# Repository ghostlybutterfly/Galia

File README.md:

# Galia
Modular split ergonomic keyboard system with each half consisting of a central motherboard and a hot-swappable key cluster daughterboard to allow for maximum flexibility.

### Motherboard

- Current version: V0.2.
- Schematic [here](https://kicanvas.org/?repo=https%3A%2F%2Fgithub.com%2Fghostlybutterfly%2FGalia%2Fblob%2FV0_dev%2FMotherboard%2FMotherboard.kicad_sch). 
- Board layout [here](https://kicanvas.org/?repo=https%3A%2F%2Fgithub.com%2Fghostlybutterfly%2FGalia%2Ftree%2FV0_dev%2FMotherboard).
### Daughterboard (Cantaloupe)
Current version: N/A (wip).

## Disclaimer
This keyboard is licensed under [CERN-OHL-S-2.0](https://cern-ohl.web.cern.ch/) and is compatible with both [QMK Firmware](https://qmk.fm/) and [ZMK Firmware](https://zmk.dev).

## Key Features
### Motherboard
* Fully reversible, compact (32.0x48.0mm), and designed to fit onto the top inner corner of a split keyboard.
* On-board STM32G0B1CCU7 processor.
* ESD-protected USB-C input port and USB-C split comms ports with ideal diode configuration for reverse current protection on VBUS input.
* Connects to daughterboard through fully ESD-protected 2.54mm pitch 02x08 pogo header in [VIK](https://github.com/sadekbaroudi/vik) breakout layout with three additional GPIO and reset button pin.
* 4-layer (signal/ground/power/signal) PCB, guard ring around PCB, and star ground connection point in between USB port shields to reduce EMI.
* VBUS input rail limited to ~500mA and 5V output rail limited to ~188mA through the use of TPS2553-1 current limiting switches with reverse voltage protection. VBUS requires power cycling to restart the device upon overcurrent, +5V can be power-cycled through firmware with EN pin controlled through firmware to reduce RGB LED quiescent current draw.
* 2x05 1.27mm Samtec IDC SWD header for debugging purposes or [Paw-Connect](https://github.com/LeoDJ/Paw-Connect) TC-2030NL header - both fit in the same space and are effectively interchangeable
* On-board button[Acheron](https://acheronproject.com/reset_article_1/reset_article_1/#52-substituting-the-jfet) single-button reset circuit.
* JLC basic assembly compatible as long as USB ports are not soldered on.

### Daughterboard (TBC)
* Matrix scan planned to be implemented through 74HC595 SIPO shift registers for low power draw and compatibility with ZMK interrupt functionality.
* Also compatible with charlieplex, duplex, and standard matrix layouts.
* WS2812 and AP102 (QMK only) LED support.
* Additional [VIK](https://github.com/sadekbaroudi/vik) header support if desired.
* USART1, USART3, and reset circuit pins routed to pogo pin header to allow for relocation of split comms receptacle and reset button on daughterboard.

## Pogo header pinout
| Function/description                  | Pin name | Row 1 | Row 2 | Pin name | Function/description                  |
| ------------------------------------- | -------- | ----- | ----- | -------- | ------------------------------------- |
| Active high, hold for 1.6s for DFU    | N/A      | RST   | GPIO5 | B8       | SPI2 SCK/TIM4 CH3/I2C1 SCL            |
| USART1 TX/SPI2 MISO/I2C1 SCL/TIM1 CH3 | B6       | GPIO3 | GPIO4 | B7       | USART1 RX/SPI2 MOSI/TIM4 CH2/I2C1 SDA |
| 200mA max draw across system          | N/A      | 3V3   | GND   | N/A      | N/A                                   |
| I2C2 SDA                              | B4       | SDA   | SCL   | B3       | I2C2 SCL                              |
| SPI2 MOSI/TIM2 CH4                    | B11      | RGB   | 5V    | N/A      | 188mA max draw by daughterboard       |
| USART3 TX/SPI2 MISO/ACD IN10          | B2       | GPIO1 | MOSI  | A7       | SPI1 MOSI                             |
| USART3 RX/TIM3 CH3/TIM1 CH2N/ADC IN8  | B0       | GPIO2 | CS    | A4       | SPI1 NSS                              |
| SPI1 MISO                             | A6       | MISO  | SCK   | A5       | SPI1 SCK                              |

## VIK keyboard certification card
| Category                 | Classification          | Response           |
| -----------------------  | ----------------------- | ------------------ |
| FPC connector            | Required                | 2.54mm pogo header |
| Breakout pins            | Recommended             | :heavy_check_mark: |
| Supplies: SPI            | Strongly recommended    | :heavy_check_mark: |
| Supplies: I2C            | Strongly recommended    | :heavy_check_mark: |
| I2C on main PCB          | Discouraged             | :x:                |
| I2C pull ups             | Informative             | :x:                |
| Supplies: RGB            | Strongly recommended    | :heavy_check_mark: |
| Supplies: Extra GPIO 1   | Required                | Analog/Digital     |
| Supplies: Extra GPIO 2   | Required                | Analog/Digital     |

## Changelog
* 2026/09/26: V0.3 motherboard update complete. Reduced size again, rerouted board and changed shape slightly. Removed one mounting hole and centred the other between the USB ports. Changed input fuse and external +5V output to TPS2553-1 latching power switch with reverse voltage/current protection. Removed AO3401 and LMV321 discrete reverse current protection at VBUS input. Reduced size of VBUS and VSPLIT ferrite bead and transistors in the Acheron reset circuit. Made Acheron reset circuit reach DFU faster. 
* 2026/09/21: V0.2 motherboard update complete. Significantly decreased size. GPIO3, GPIO4 and GPIO5 pins changed. Increased size of pogo pin header pads. Removed extra IO header. Replaced 2x03 2.54mm programming header and TC2030-NL with 2x05 1.27mm Samtec IDC header. Replaced reset switch with smaller Alps SKSNLP mid-mount switch. Added layer marker. Changed repository file structure.
* 2026/09/17: Fixed gap in guard rail.
* 2026/09/16: V0.1 motherboard initial commit.

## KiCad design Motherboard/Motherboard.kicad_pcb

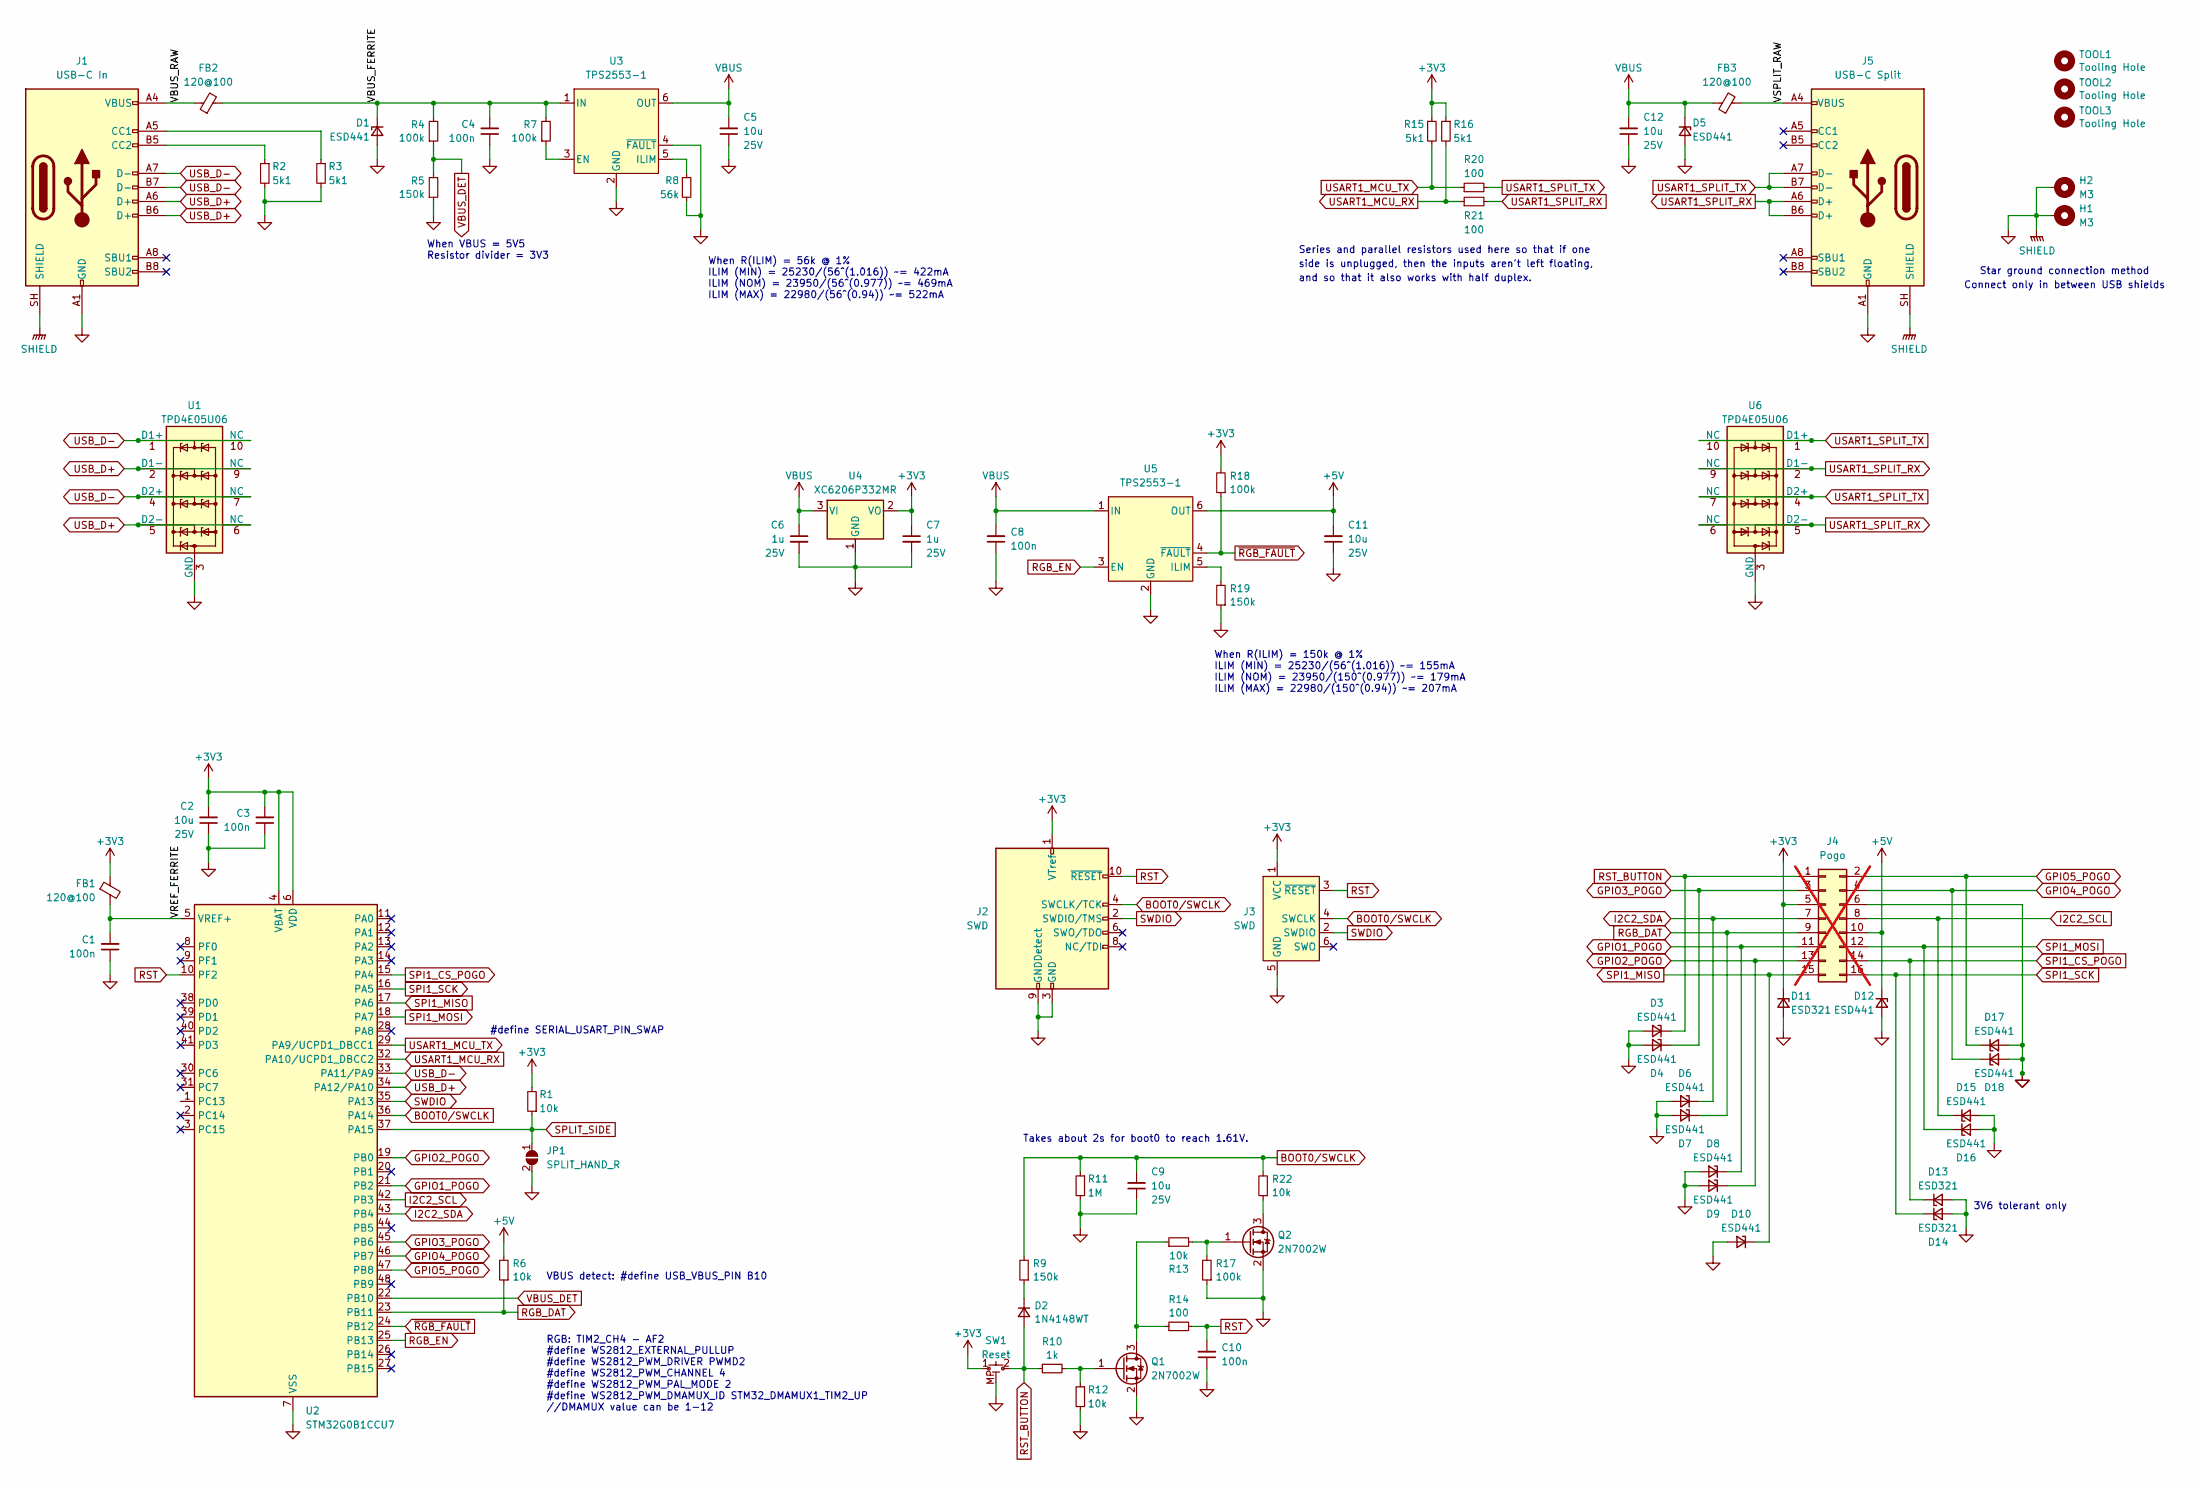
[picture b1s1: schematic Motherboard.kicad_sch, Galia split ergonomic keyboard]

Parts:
C1, C3, C4, C8, C10: 100n; C_0402_1005Metric; Rating 50V; MPN CL05B104KB54PNC; LCSC C307331
C2, C5, C9, C11, C12: 10u; C_0603_1608Metric; Rating 25V; MPN CL10A106MA8NRNC; LCSC C96446
C6, C7: 1u; C_0402_1005Metric; Rating 25V; MPN CL05A105KA5NQNC; LCSC C52923
D1, D3, D4, D5, D6, D7, D8, D9, D10, D12, D15, D16, D17, D18: ESD441; X1SON_0.6x1mm_P0.65mm_Texas_DPY0002A; MPN ESD441DPYR; LCSC C53161160
D2: 1N4148WT; D_SOD-523; MPN 1N4148WT; LCSC C7420320
D11, D13, D14: ESD321; X1SON_0.6x1mm_P0.65mm_Texas_DPY0002A; MPN ESD321DPYR; LCSC C2868952
FB1, FB2, FB3: 120@100; L_0402_1005Metric; MPN MPZ1005S121ET000; LCSC C275477
H1, H2: M3; MountingHole_3.2mm_M3_Pad_Via; MPN N/A; LCSC N/A
J1: USB-C In; USB_C_Receptacle_Molex_2169900001; MPN GT-USB-7014D; LCSC C2843969
J2: SWD; PinHeader_2x05_P1.27mm_Vertical_Samtec-FTSH-105-01-L-D-K; MPN FTSH-105-01-L-D-K; LCSC N/A
J3: SWD; Paw-Connect_RevB_TC2030-IDC-NL_2x03_P1.27mm_Vertical
J4: Pogo; PinHeader_2x08_2.54mm_MillMax_PogoTarget_419-10-216-00-0010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; MPN 419-10-214-00-001000; LCSC N/A; not fitted
J5: USB-C Split; USB_C_Receptacle_Molex_2169900001; MPN GT-USB-7014D; LCSC C2843969
JP1: SPLIT_HAND_R; SolderJumper-2_P1.2mm_Open_Pad1.0x1.4mm; MPN N/A; LCSC N/A
Q1, Q2: 2N7002W; SOT-323_SC-70-3; MPN 2N7002W; LCSC C7420322
R1, R6, R12, R13, R22: 10k; R_0402_1005Metric; MPN 0402WGF1002TCE; LCSC C25744
R2, R3, R15, R16: 5k1; R_0402_1005Metric; MPN 0402WGF5101TCE; LCSC C25905
R4, R7, R17, R18: 100k; R_0402_1005Metric; MPN 0402WGF1003TCE; LCSC C25741
R5, R9, R19: 150k; R_0402_1005Metric; MPN 0402WGF1503TCE; LCSC C25755
R8: 56k; R_0402_1005Metric; MPN 0402WGF5602TCE; LCSC C25796
R10: 1k; R_0402_1005Metric; MPN 0402WGF1001TCE; LCSC C11702
R11: 1M; R_0402_1005Metric; MPN 0402WGF1004TCE; LCSC C26083
R14, R20, R21: 100; R_0402_1005Metric; MPN 0402WGF1000TCE; LCSC C25076
SW1: Reset; SW_Alps_SKSNLM_SKSNLP; MPN SKSNLPE010; LCSC C53113391
TOOL1, TOOL2, TOOL3: Tooling Hole; MountingHole_JLC-Tooling; MPN N/A; LCSC N/A
U1, U6: TPD4E05U06; USON-10_2.5x1.0mm_P0.5mm; MPN TPD4E05U06QDQARQ1; LCSC C81353
U2: STM32G0B1CCU7; QFN-48-1EP_7x7mm_P0.5mm_EP5.6x5.6mm; MPN STM32G0B1CCU7; LCSC C29759424
U3, U5: TPS2553-1; WSON-6-1EP_2x2mm_P0.65mm_EP1x1.6mm
U4: XC6206P332MR; SOT-23-3; MPN XC6206P332MR-G; LCSC C5446

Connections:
+3V3: C2.2, C3.2, C7.1, D11.1 (K), FB1.1, J2.1 (VTref), J3.1 (VCC), J4.5, R1.2, R15.1, R16.1, R18.2, SW1.1 (A), U2.4 (VBAT), U2.6 (VDD), U4.2 (VO)
+5V: C11.2, D12.1 (K), J4.10, R6.2, U5.6 (OUT)
/VBUS_FERRITE: C4.2, D1.1 (K), FB2.2, R4.2, R7.2, U3.1 (IN)
/VBUS_RAW: FB2.1, J1.A4 (VBUS), J1.A9 (VBUS), J1.B4 (VBUS), J1.B9 (VBUS)
/VREF_FERRITE: C1.2, FB1.2, U2.5 (VREF+)
/VSPLIT_RAW: FB3.2, J5.A4 (VBUS), J5.A9 (VBUS), J5.B4 (VBUS), J5.B9 (VBUS)
BOOT0/SWCLK: C9.2, J2.4 (SWCLK/TCK), J3.4 (SWCLK), R9.2, R11.1, R22.2, U2.36 (PA14)
GND: C1.1, C2.1, C3.1, C4.1, C5.1, C6.2, C7.2, C8.1, C9.1, C10.1, C11.1, C12.1, D1.2 (A), D3.2 (A), D4.2 (A), D5.2 (A), D6.2 (A), D7.2 (A), D8.2 (A), D9.2 (A), D10.2 (A), D11.2 (A), D12.2 (A), D13.2 (A), D14.2 (A), D15.2 (A), D16.2 (A), D17.2 (A), D18.2 (A), H1.1 (1_1), H2.1 (1_1), J1.A1 (GND), J1.A12 (GND), J1.B1 (GND), J1.B12 (GND), J1.SH (SHIELD), J2.3 (GND), J2.5 (GND), J2.9 (GNDDetect), J3.5 (GND), J4.6, J5.A1 (GND), J5.A12 (GND), J5.B1 (GND), J5.B12 (GND), J5.SH (SHIELD), JP1.2 (B), Q1.2 (S), Q2.2 (S), R2.2, R3.2, R5.1, R8.2, R11.2, R12.2, R17.1, R19.1, SW1.MP (A), U1.3 (GND), U1.8 (GND), U2.7 (VSS), U2.49 (VSS), U3.2 (GND), U3.4 (~FAULT), U3.7 (EP), U4.1 (GND), U5.2 (GND), U5.7 (EP), U6.3 (GND), U6.8 (GND)
GPIO1_POGO: D8.1 (K), J4.11, U2.21 (PB2)
GPIO2_POGO: D9.1 (K), J4.13, U2.19 (PB0)
GPIO3_POGO: D4.1 (K), J4.3, U2.45 (PB6)
GPIO4_POGO: D18.1 (K), J4.4, U2.46 (PB7)
GPIO5_POGO: D17.1 (K), J4.2, U2.47 (PB8)
I2C2_SCL: D15.1 (K), J4.8, U2.42 (PB3)
I2C2_SDA: D6.1 (K), J4.7, U2.43 (PB4)
unnamed: D2.1 (K), R9.1
unnamed: J1.A5 (CC1), R3.1
unnamed: J1.B5 (CC2), R2.1
unnamed: Q1.3 (D), R13.1, R14.1
unnamed: Q1.1 (G), R10.2, R12.1
unnamed: Q2.3 (D), R22.1
unnamed: Q2.1 (G), R13.2, R17.2
unnamed: R7.1, U3.3 (EN)
unnamed: R8.1, U3.5 (ILIM)
unnamed: R19.2, U5.5 (ILIM)
RGB_DAT: D7.1 (K), J4.9, R6.1, U2.23 (PB11)
RGB_EN: U2.25 (PB13), U5.3 (EN)
RST: C10.2, J2.10 (~RESET), J3.3 (~RESET), R14.2, U2.10 (PF2)
RST_BUTTON: D2.2 (A), D3.1 (K), J4.1, R10.1, SW1.2 (B)
SPI1_CS_POGO: D13.1 (K), J4.14, U2.15 (PA4)
SPI1_MISO: D10.1 (K), J4.15, U2.17 (PA6)
SPI1_MOSI: D16.1 (K), J4.12, U2.18 (PA7)
SPI1_SCK: D14.1 (K), J4.16, U2.16 (PA5)
SPLIT_SIDE: JP1.1 (A), R1.1, U2.37 (PA15)
SWDIO: J2.2 (SWDIO/TMS), J3.2 (SWDIO), U2.35 (PA13)
USART1_MCU_RX: R16.2, R21.1, U2.32 (PA10/UCPD1_DBCC2)
USART1_MCU_TX: R15.2, R20.1, U2.29 (PA9/UCPD1_DBCC1)
USART1_SPLIT_RX: J5.A6 (D+), J5.B6 (D+), R21.2, U6.2 (D1-), U6.5 (D2-), U6.6 (NC), U6.9 (NC)
USART1_SPLIT_TX: J5.A7 (D-), J5.B7 (D-), R20.2, U6.1 (D1+), U6.4 (D2+), U6.7 (NC), U6.10 (NC)
USB_D+: J1.A6 (D+), J1.B6 (D+), U1.2 (D1-), U1.5 (D2-), U1.6 (NC), U1.9 (NC), U2.34 (PA12/PA10)
USB_D-: J1.A7 (D-), J1.B7 (D-), U1.1 (D1+), U1.4 (D2+), U1.7 (NC), U1.10 (NC), U2.33 (PA11/PA9)
VBUS: C5.2, C6.1, C8.2, C12.2, D5.1 (K), FB3.1, U3.6 (OUT), U4.3 (VI), U5.1 (IN)
VBUS_DET: R4.1, R5.2, U2.22 (PB10)
~RGB_FAULT: R18.1, U2.24 (PB12), U5.4 (~FAULT)

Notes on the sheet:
3V6 tolerant only
#define WS2812_EXTERNAL_PULLUP #define WS2812_PWM_DRIVER PWMD2 #define WS2812_PWM_CHANNEL 4 #define WS2812_PWM_PAL_MODE 2 #define WS2812_PWM_DMAMUX_ID STM32_DMAMUX1_TIM2_UP //DMAMUX value can be 1-12
When R(ILIM) = 56k @ 1% ILIM (MIN) = 25230/(56^(1.016)) ~= 422mA ILIM (NOM) = 23950/(56^(0.977)) ~= 469mA ILIM (MAX) = 22980/(56^(0.94)) ~= 522mA
Takes about 2s for boot0 to reach 1.61V.
RGB: TIM2_CH4 - AF2
Series and parallel resistors used here so that if one
VBUS detect: #define USB_VBUS_PIN B10
side is unplugged, then the inputs aren't left floating,
and so that it also works with half duplex.
When VBUS = 5V5 Resistor divider = 3V3
Connect only in between USB shields
#define SERIAL_USART_PIN_SWAP
When R(ILIM) = 150k @ 1% ILIM (MIN) = 25230/(56^(1.016)) ~= 155mA ILIM (NOM) = 23950/(150^(0.977)) ~= 179mA ILIM (MAX) = 22980/(150^(0.94)) ~= 207mA
Star ground connection method

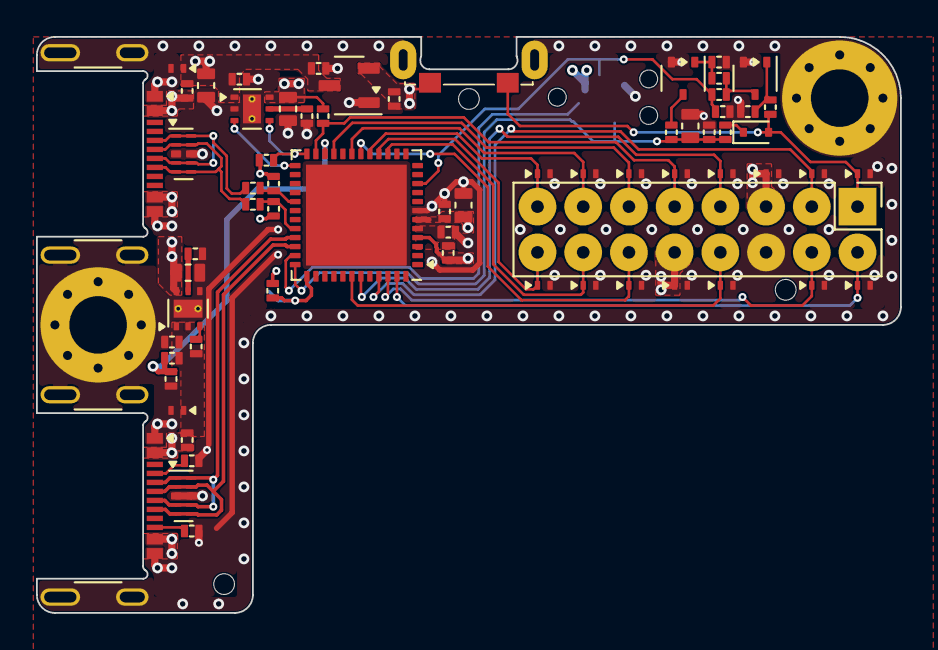
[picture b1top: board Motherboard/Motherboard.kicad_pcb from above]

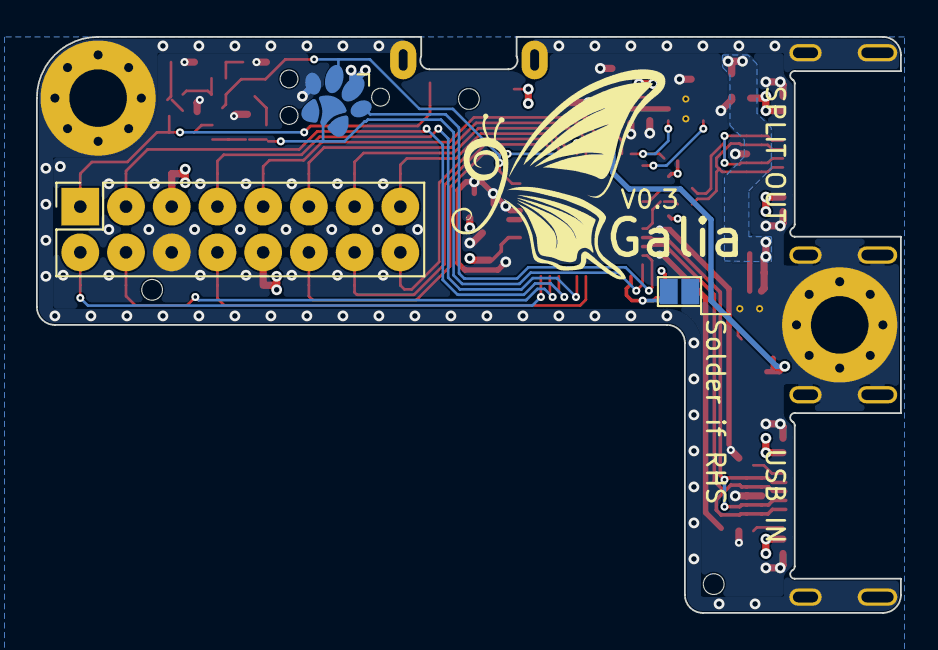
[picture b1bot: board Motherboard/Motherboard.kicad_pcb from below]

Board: 4 copper layers, 48.0 x 32.0 mm, 74 parts (3 on the bottom side), 44 nets.

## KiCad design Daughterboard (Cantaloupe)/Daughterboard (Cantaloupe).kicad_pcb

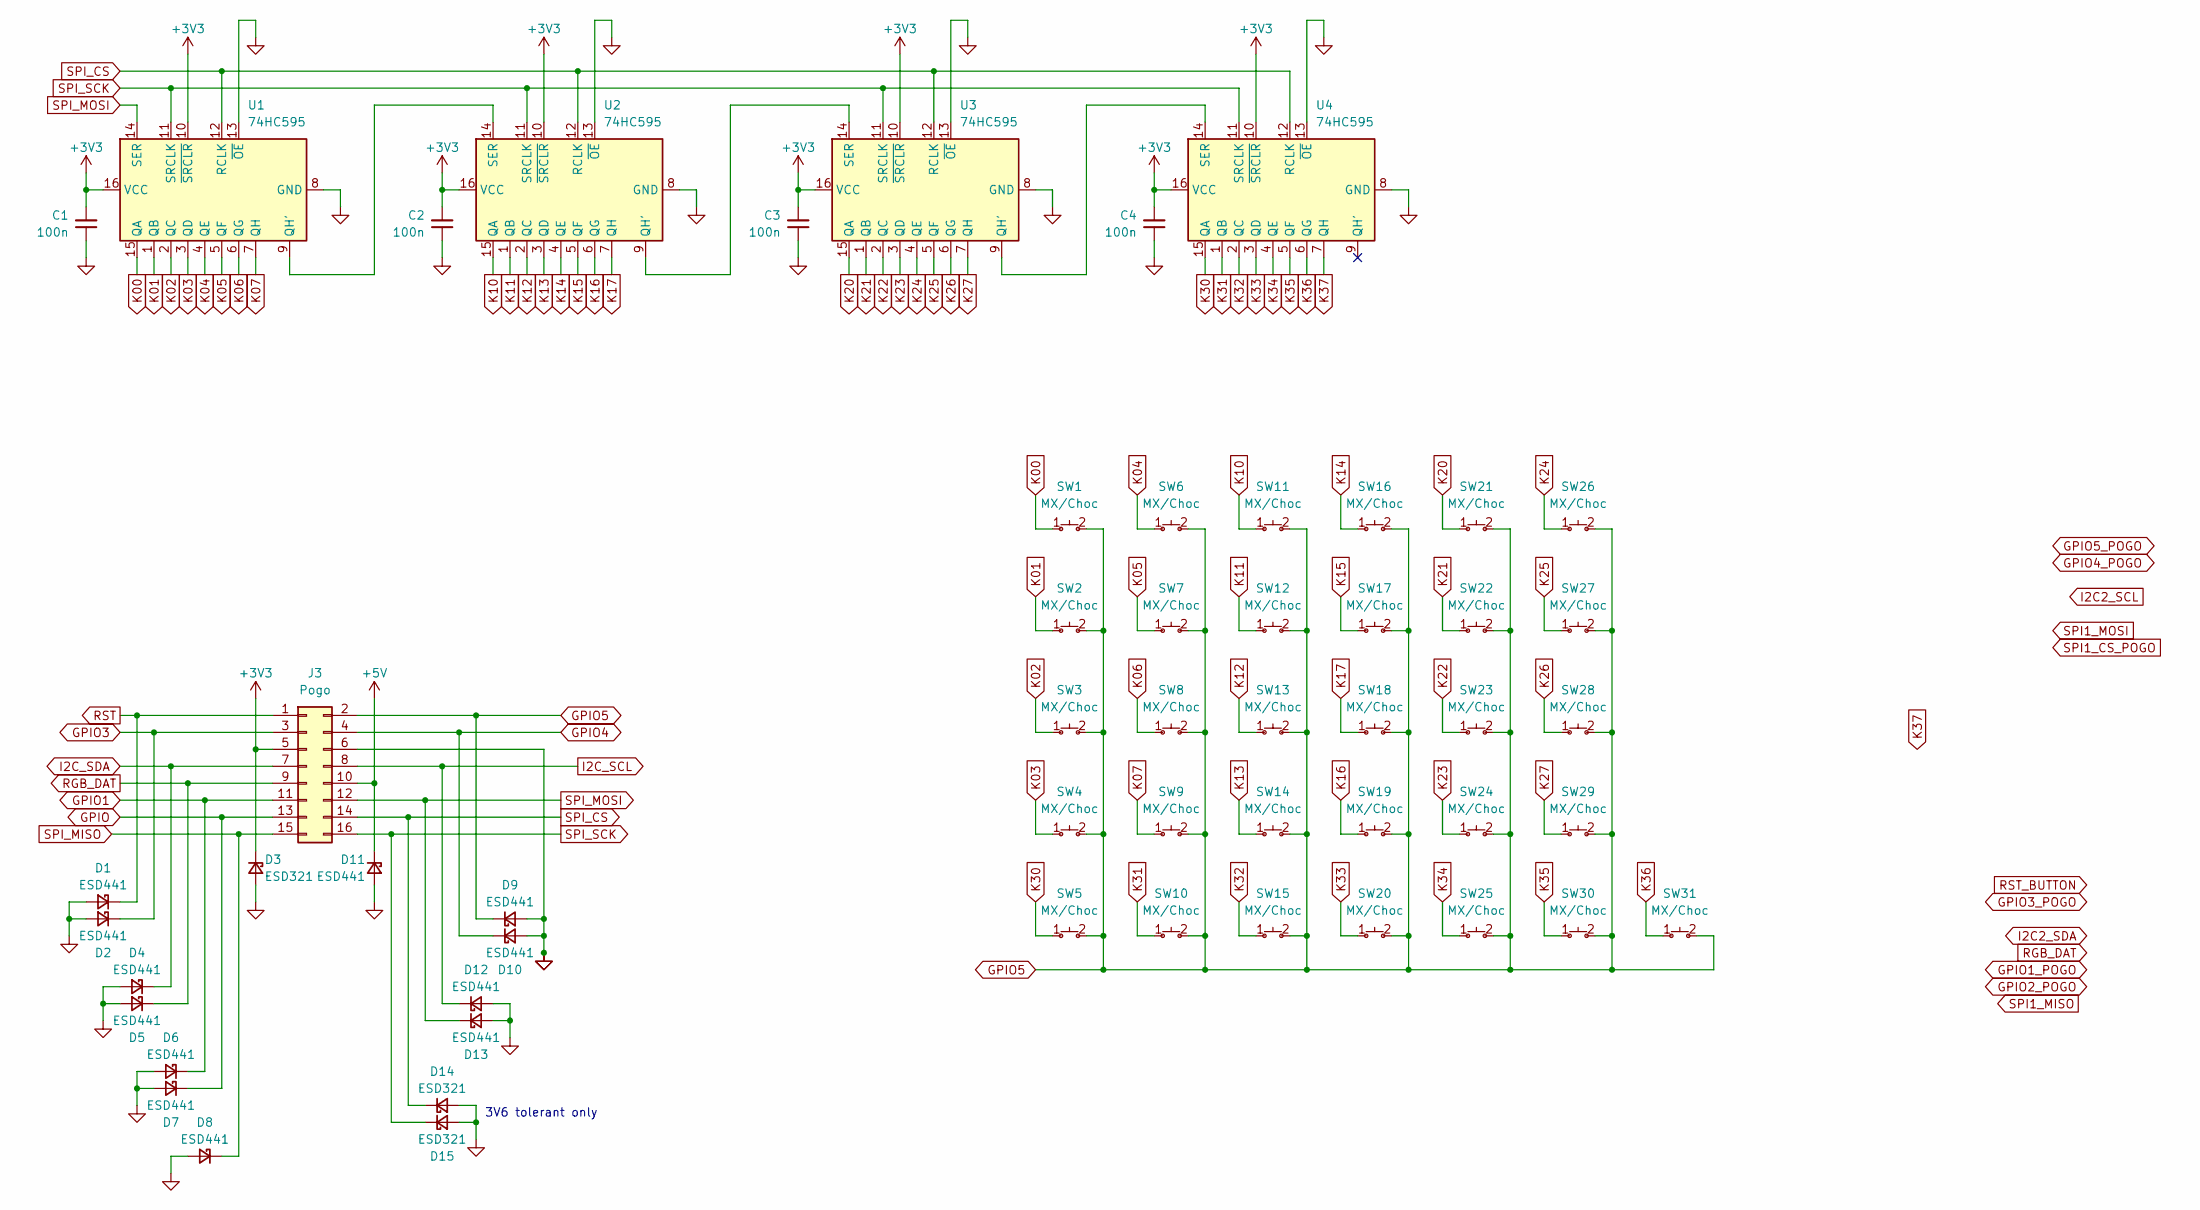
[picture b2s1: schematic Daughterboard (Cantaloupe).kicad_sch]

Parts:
C1, C2, C3, C4: 100n; C_0402_1005Metric; Voltage 50V; MPN CL05B104KB54PNC; LCSC C307331
D1, D2, D4, D5, D6, D7, D8, D9, D10, D11, D12, D13: ESD441; X1SON_0.6x1mm_P0.65mm_Texas_DPY0002A; MPN ESD441DPYR; LCSC C53161160
D3, D14, D15: ESD321; X1SON_0.6x1mm_P0.65mm_Texas_DPY0002A; MPN ESD321DPYR; LCSC C2868952
J3: Pogo; PinHeader_2x08_2.54mm_MillMax_PogoPin_823-22-016-10-002101_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; MPN 419-10-214-00-001000
SW1, SW2, SW3, SW4, SW5, SW6, SW7, SW8, SW9, SW10, SW11, SW12, SW13, SW14, SW15, SW16, SW17, SW18, SW19, SW20, SW21, SW22, SW23, SW24, SW25, SW26, SW27, SW28, SW29, SW30, SW31: MX/Choc; SW_MX-Choc_1U_Hotswap_Flippable
U1, U2, U3, U4: 74HC595; DHVQFN-16-1EP_2.5x3.5mm_P0.5mm_EP1x2mm; MPN 74HC595BQ,115; LCSC C730243

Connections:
+3V3: C1.2, C2.2, C3.2, C4.2, D3.1 (K), J3.5, U1.10 (~SRCLR), U1.16 (VCC), U2.10 (~SRCLR), U2.16 (VCC), U3.10 (~SRCLR), U3.16 (VCC), U4.10 (~SRCLR), U4.16 (VCC)
+5V: D11.1 (K), J3.10
GND: C1.1, C2.1, C3.1, C4.1, D1.2 (A), D2.2 (A), D3.2 (A), D4.2 (A), D5.2 (A), D6.2 (A), D7.2 (A), D8.2 (A), D9.2 (A), D10.2 (A), D11.2 (A), D12.2 (A), D13.2 (A), D14.2 (A), D15.2 (A), J3.6, U1.8 (GND), U1.13 (~OE), U1.17 (EP), U2.8 (GND), U2.13 (~OE), U2.17 (EP), U3.8 (GND), U3.13 (~OE), U3.17 (EP), U4.8 (GND), U4.13 (~OE), U4.17 (EP)
GPIO: D7.1 (K), J3.13
GPIO1: D6.1 (K), J3.11
GPIO3: D2.1 (K), J3.3
GPIO4: D10.1 (K), J3.4
GPIO5: D9.1 (K), J3.2, SW1.2 (B), SW2.2 (B), SW3.2 (B), SW4.2 (B), SW5.2 (B), SW6.2 (B), SW7.2 (B), SW8.2 (B), SW9.2 (B), SW10.2 (B), SW11.2 (B), SW12.2 (B), SW13.2 (B), SW14.2 (B), SW15.2 (B), SW16.2 (B), SW17.2 (B), SW18.2 (B), SW19.2 (B), SW20.2 (B), SW21.2 (B), SW22.2 (B), SW23.2 (B), SW24.2 (B), SW25.2 (B), SW26.2 (B), SW27.2 (B), SW28.2 (B), SW29.2 (B), SW30.2 (B), SW31.2 (B)
I2C_SCL: D12.1 (K), J3.8
I2C_SDA: D4.1 (K), J3.7
K00: SW1.1 (A), U1.15 (QA)
K01: SW2.1 (A), U1.1 (QB)
K02: SW3.1 (A), U1.2 (QC)
K03: SW4.1 (A), U1.3 (QD)
K04: SW6.1 (A), U1.4 (QE)
K05: SW7.1 (A), U1.5 (QF)
K06: SW8.1 (A), U1.6 (QG)
K07: SW9.1 (A), U1.7 (QH)
K10: SW11.1 (A), U2.15 (QA)
K11: SW12.1 (A), U2.1 (QB)
K12: SW13.1 (A), U2.2 (QC)
K13: SW14.1 (A), U2.3 (QD)
K14: SW16.1 (A), U2.4 (QE)
K15: SW17.1 (A), U2.5 (QF)
K16: SW19.1 (A), U2.6 (QG)
K17: SW18.1 (A), U2.7 (QH)
K20: SW21.1 (A), U3.15 (QA)
K21: SW22.1 (A), U3.1 (QB)
K22: SW23.1 (A), U3.2 (QC)
K23: SW24.1 (A), U3.3 (QD)
K24: SW26.1 (A), U3.4 (QE)
K25: SW27.1 (A), U3.5 (QF)
K26: SW28.1 (A), U3.6 (QG)
K27: SW29.1 (A), U3.7 (QH)
K30: SW5.1 (A), U4.15 (QA)
K31: SW10.1 (A), U4.1 (QB)
K32: SW15.1 (A), U4.2 (QC)
K33: SW20.1 (A), U4.3 (QD)
K34: SW25.1 (A), U4.4 (QE)
K35: SW30.1 (A), U4.5 (QF)
K36: SW31.1 (A), U4.6 (QG)
K37: U4.7 (QH)
unnamed: U1.9 (QH'), U2.14 (SER)
unnamed: U2.9 (QH'), U3.14 (SER)
unnamed: U3.9 (QH'), U4.14 (SER)
RGB_DAT: D5.1 (K), J3.9
RST: D1.1 (K), J3.1
SPI_CS: D14.1 (K), J3.14, U1.12 (RCLK), U2.12 (RCLK), U3.12 (RCLK), U4.12 (RCLK)
SPI_MISO: D8.1 (K), J3.15
SPI_MOSI: D13.1 (K), J3.12, U1.14 (SER)
SPI_SCK: D15.1 (K), J3.16, U1.11 (SRCLK), U2.11 (SRCLK), U3.11 (SRCLK), U4.11 (SRCLK)

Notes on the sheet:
3V6 tolerant only

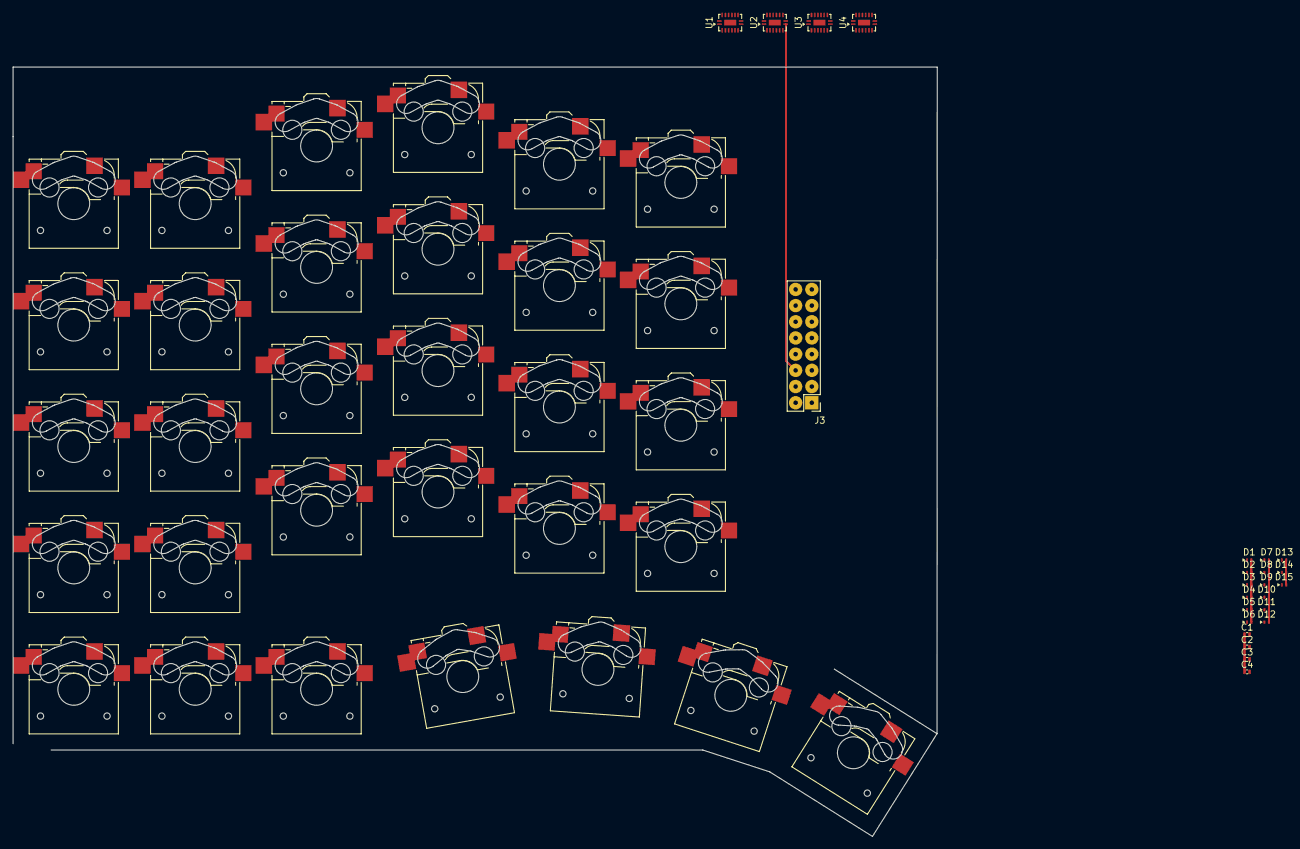
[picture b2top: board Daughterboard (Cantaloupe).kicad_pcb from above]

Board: 2 copper layers, 55 parts (0 on the bottom side), 50 nets.

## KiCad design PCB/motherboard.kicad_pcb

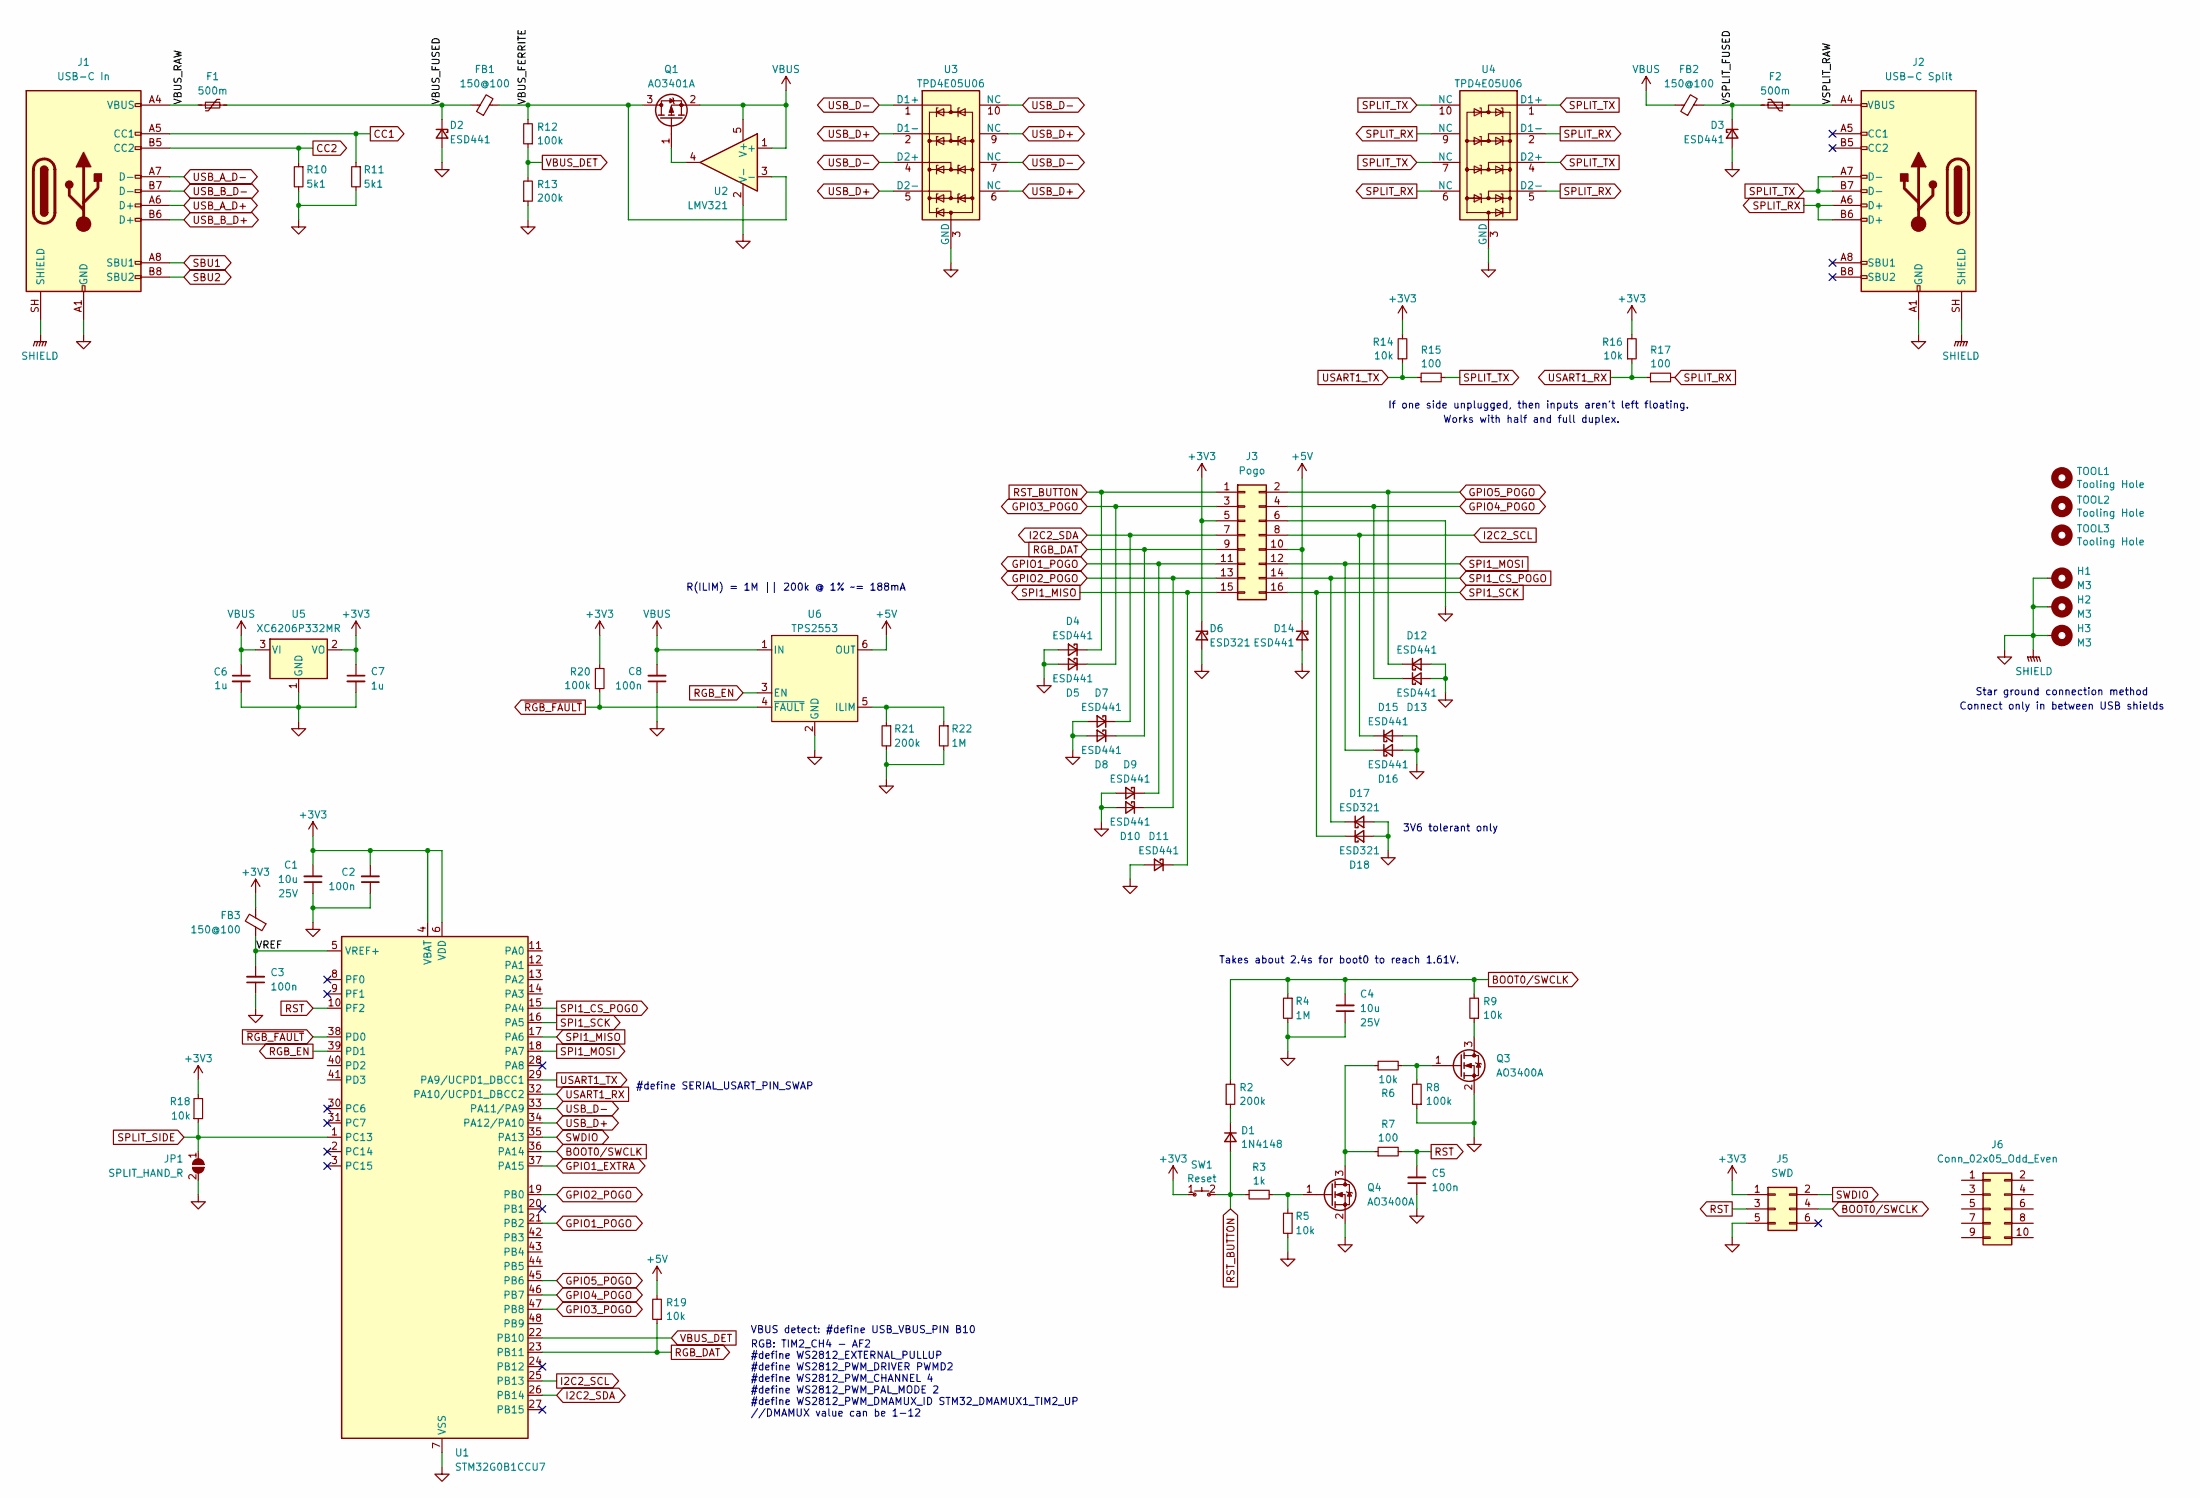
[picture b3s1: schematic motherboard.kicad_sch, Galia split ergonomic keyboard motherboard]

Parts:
C1, C4: 10u; C_0603_1608Metric; Voltage 25V; MPN CL10A106MA8NRNC; LCSC C96446
C2, C3, C5, C8: 100n; C_0402_1005Metric; Voltage 50V; MPN CL05B104KB54PNC; LCSC C307331
C6, C7: 1u; C_0402_1005Metric; Voltage 25V; MPN CL05A105KA5NQNC; LCSC C52923
D1: 1N4148; D_SOD-323; MPN 1N4148WS; LCSC C2128
D2, D3, D4, D5, D7, D8, D9, D10, D11, D12, D13, D14, D15, D16: ESD441; Texas_DPY0002A_0.6x1mm_P0.65mm; MPN ESD441DPYR; LCSC C53161160
D6, D17, D18: ESD321; Texas_DPY0002A_0.6x1mm_P0.65mm; MPN ESD321DPYR; LCSC C2868952
F1, F2: 500m; Fuse_0603_1608Metric; MPN MF-FSMF050X-2; LCSC C210357
FB1, FB2, FB3: 150@100; L_0603_1608Metric; MPN MPZ1608Y151BTD25; LCSC C404681
H1, H2, H3: M3; MountingHole_3.2mm_M3_Pad_Via
J1: USB-C In; HRO_TYPE-C-31-M-13x; MPN TYPE-C-31-M-13C; LCSC C2848620
J2: USB-C Split; HRO_TYPE-C-31-M-13x; MPN TYPE-C-31-M-13C; LCSC C2848620
J3: Pogo; MillMax_2x08_2.54mm_Pogo_Target_419-10-216-00-001000-Double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; MPN 419-10-214-00-001000
J5: SWD; PinHeader_2x03_P2.54mm_Vertical-Double_Sided
J6: Conn_02x05_Odd_Even
JP1: SPLIT_HAND_R; SolderJumper-2_P1.2mm_Open_Pad1.0x1.4mm
Q1: AO3401A; SOT-23-3; MPN AO3401A; LCSC C15127
Q3, Q4: AO3400A; SOT-23-3; MPN AO3400A; LCSC C20917
R2, R13, R21: 200k; R_0402_1005Metric; MPN 0402WGF2003TCE; LCSC C25764
R3: 1k; R_0402_1005Metric; MPN 0402WGF1001TCE; LCSC C11702
R4, R22: 1M; R_0402_1005Metric; MPN 0402WGF1004TCE; LCSC C26083
R5, R6, R9, R14, R16, R18, R19: 10k; R_0402_1005Metric; MPN 0402WGF1002TCE; LCSC C25744
R7, R15, R17: 100; R_0402_1005Metric; MPN 0402WGF1000TCE; LCSC C25076
R8, R12, R20: 100k; R_0402_1005Metric; MPN 0402WGF1003TCE; LCSC C25741
R10, R11: 5k1; R_0402_1005Metric; MPN 0402WGF5101TCE; LCSC C25905
SW1: Reset; SW_Alps_SKHLLA-Double_Sided; MPN SKHLLA; LCSC C318884
TOOL1, TOOL2, TOOL3: Tooling Hole; MountingHole_JLC-Tooling
U1: STM32G0B1CCU7; QFN-48-1EP_7x7mm_P0.5mm_EP5.6x5.6mm; MPN STM32G0B1CCU7; LCSC C29759424
U2: LMV321; SOT-23-5; MPN LMV321IDBVR; LCSC C7972
U3, U4: TPD4E05U06; USON-10_2.5x1.0mm_P0.5mm; MPN TPD4E05U06QDQARQ1; LCSC C81353
U5: XC6206P332MR; SOT-23-3; MPN XC6206P332MR-G; LCSC C5446
U6: TPS2553; SOT-23-6; MPN TPS2553DDBVR; LCSC C521201

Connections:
+3V3: C1.2, C2.2, C7.1, D6.1 (K), FB3.2, J3.5, J5.1, R14.2, R16.2, R18.2, R20.2, SW1.1 (A), U1.4 (VBAT), U1.6 (VDD), U5.2 (VO)
+5V: D14.1 (K), J3.10, R19.2, U6.6 (OUT)
/VBUS_FERRITE: FB1.2, Q1.3 (D), R12.2, U2.3 (-)
/VBUS_FUSED: D2.1 (K), F1.2, FB1.1
/VBUS_RAW: F1.1, J1.A4 (VBUS), J1.A9 (VBUS), J1.B4 (VBUS), J1.B9 (VBUS)
/VREF: C3.2, FB3.1, U1.5 (VREF+)
/VSPLIT_FUSED: D3.1 (K), F2.2, FB2.2
/VSPLIT_RAW: F2.1, J2.A4 (VBUS), J2.A9 (VBUS), J2.B4 (VBUS), J2.B9 (VBUS)
BOOT0/SWCLK: C4.2, J5.4, R2.2, R4.1, R9.2, U1.36 (PA14)
CC1: J1.A5 (CC1), R11.1
CC2: J1.B5 (CC2), R10.1
GND: C1.1, C2.1, C3.1, C4.1, C5.1, C6.2, C7.2, C8.1, D2.2 (A), D3.2 (A), D4.2 (A), D5.2 (A), D6.2 (A), D7.2 (A), D8.2 (A), D9.2 (A), D10.2 (A), D11.2 (A), D12.2 (A), D13.2 (A), D14.2 (A), D15.2 (A), D16.2 (A), D17.2 (A), D18.2 (A), H1.1 (1_1), H2.1 (1_1), H3.1 (1_1), J1.A1 (GND), J1.A12 (GND), J1.B1 (GND), J1.B12 (GND), J1.SH (SHIELD), J2.A1 (GND), J2.A12 (GND), J2.B1 (GND), J2.B12 (GND), J2.SH (SHIELD), J3.6, J5.5, JP1.2 (B), Q3.2 (S), Q4.2 (S), R4.2, R5.2, R8.1, R10.2, R11.2, R13.1, R21.2, R22.2, U1.7 (VSS), U1.49 (VSS), U2.2 (V-), U3.3 (GND), U3.8 (GND), U4.3 (GND), U4.8 (GND), U5.1 (GND), U6.2 (GND)
GPIO1_EXTRA: U1.37 (PA15)
GPIO1_POGO: D9.1 (K), J3.11, U1.21 (PB2)
GPIO2_POGO: D10.1 (K), J3.13, U1.19 (PB0)
GPIO3_POGO: D5.1 (K), J3.3, U1.47 (PB8)
GPIO4_POGO: D13.1 (K), J3.4, U1.46 (PB7)
GPIO5_POGO: D12.1 (K), J3.2, U1.45 (PB6)
I2C2_SCL: D15.1 (K), J3.8, U1.25 (PB13)
I2C2_SDA: D7.1 (K), J3.7, U1.26 (PB14)
unnamed: D1.1 (K), R2.1
unnamed: Q1.1 (G), U2.4
unnamed: Q3.3 (D), R9.1
unnamed: Q3.1 (G), R6.2, R8.2
unnamed: Q4.3 (D), R6.1, R7.1
unnamed: Q4.1 (G), R3.2, R5.1
unnamed: R21.1, R22.1, U6.5 (ILIM)
RGB_DAT: D8.1 (K), J3.9, R19.1, U1.23 (PB11)
RGB_EN: U1.39 (PD1), U6.3 (EN)
RST: C5.2, J5.3, R7.2, U1.10 (PF2)
RST_BUTTON: D1.2 (A), D4.1 (K), J3.1, R3.1, SW1.2 (B)
SBU1: J1.A8 (SBU1)
SBU2: J1.B8 (SBU2)
SPI1_CS_POGO: D17.1 (K), J3.14, U1.15 (PA4)
SPI1_MISO: D11.1 (K), J3.15, U1.17 (PA6)
SPI1_MOSI: D16.1 (K), J3.12, U1.18 (PA7)
SPI1_SCK: D18.1 (K), J3.16, U1.16 (PA5)
SPLIT_RX: J2.A6 (D+), J2.B6 (D+), R17.2, U4.2 (D1-), U4.5 (D2-), U4.6 (NC), U4.9 (NC)
SPLIT_SIDE: JP1.1 (A), R18.1, U1.1 (PC13)
SPLIT_TX: J2.A7 (D-), J2.B7 (D-), R15.2, U4.1 (D1+), U4.4 (D2+), U4.7 (NC), U4.10 (NC)
SWDIO: J5.2, U1.35 (PA13)
USART1_RX: R16.1, R17.1, U1.32 (PA10/UCPD1_DBCC2)
USART1_TX: R14.1, R15.1, U1.29 (PA9/UCPD1_DBCC1)
USB_A_D+: J1.A6 (D+)
USB_A_D-: J1.A7 (D-)
USB_B_D+: J1.B6 (D+)
USB_B_D-: J1.B7 (D-)
USB_D+: U1.34 (PA12/PA10), U3.2 (D1-), U3.5 (D2-), U3.6 (NC), U3.9 (NC)
USB_D-: U1.33 (PA11/PA9), U3.1 (D1+), U3.4 (D2+), U3.7 (NC), U3.10 (NC)
VBUS: C6.1, C8.2, FB2.1, Q1.2 (S), U2.1 (+), U2.5 (V+), U5.3 (VI), U6.1 (IN)
VBUS_DET: R12.1, R13.2, U1.22 (PB10)
~RGB_FAULT: R20.1, U1.38 (PD0), U6.4 (~FAULT)

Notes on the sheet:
3V6 tolerant only
R(ILIM) = 1M || 200k @ 1% ~= 188mA
#define WS2812_EXTERNAL_PULLUP #define WS2812_PWM_DRIVER PWMD2 #define WS2812_PWM_CHANNEL 4 #define WS2812_PWM_PAL_MODE 2 #define WS2812_PWM_DMAMUX_ID STM32_DMAMUX1_TIM2_UP //DMAMUX value can be 1-12
If one side unplugged, then inputs aren't left floating.
Takes about 2.4s for boot0 to reach 1.61V.
RGB: TIM2_CH4 - AF2
VBUS detect: #define USB_VBUS_PIN B10
Works with half and full duplex.
Connect only in between USB shields
#define SERIAL_USART_PIN_SWAP
Star ground connection method

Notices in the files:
Motherboard/Motherboard.kicad_pcb:
By Ghostly Butterfly (https://github.com/ghostlybutterfly/Galia/) under CERN-OHL-S-2.0
PCB/motherboard.kicad_pcb:
Licensed under CC BY 4.0.
